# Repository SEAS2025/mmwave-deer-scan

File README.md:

# mmWave Deer Scan

Roadside **mmWave radar** deer detection for ambulance / fleet safety — companion to [agm-taipan-deer-scan](https://github.com/SEAS2025/agm-taipan-deer-scan) (thermal).

Detect deer from FMCW point clouds using size, speed, and SNR heuristics. Designed for **TI mmWave** UART JSON output and a **simulated** feed for development without hardware.

## Features

- Point-cloud clustering on sparse mmWave returns
- Deer-shaped target scoring (length, height, lateral position, speed)
- EGPWS-style threat callouts (left / ahead / right + range tier)
- TI mmWave serial reader (JSON lines) + OpenRadar raw-ADC adapter
- Thermal fusion (confirm with agm-taipan-deer-scan) and Pi GPIO/CAN alert outputs
- Session recorder for labeled training data
- Simulated roadside scene for offline development
- **Full hardware design**: system architecture, BOM, integration diagrams,
  dimensioned enclosure drawing, and a JLCPCB-ready carrier-board Gerber package
- **Imaging R&D track**: micro-Doppler + ISAR processing skeleton on raw ADC
  (`mmwave_deer/imaging/`), with a synthetic walking-deer demo

## Documentation & design

| Doc | What |
|-----|------|
| [docs/SYSTEM_DESIGN.md](docs/SYSTEM_DESIGN.md) | architecture, sensor/compute/power, requirements, risks |
| [docs/BOM.md](docs/BOM.md) / [docs/bom.csv](docs/bom.csv) | parts, links, cost roll-up (proto ~$400, prod target ~$140) |
| [docs/INTEGRATION.md](docs/INTEGRATION.md) | block diagram, power tree, GPIO map, wiring, sequence |
| [hardware/README.md](hardware/README.md) | enclosure drawing + carrier PCB |
| [hardware/enclosure/orthographic.svg](hardware/enclosure/orthographic.svg) | dimensioned 3-view drawing |
| [hardware/pcb/carrier_board/](hardware/pcb/carrier_board/) | Gerbers + `DeerWatch-Carrier-gerbers.zip` for JLCPCB |
| [hardware/pcb/carrier_board/kicad/](hardware/pcb/carrier_board/kicad/) | KiCad 10 project, DRC-clean, KiCad-exported Gerbers + 3D render |
| [docs/VARIANT_AWR1843.md](docs/VARIANT_AWR1843.md) | 77 GHz AWR1843BOOST variant - range math, config, carrier + BOM delta |
| [docs/IMAGING_RADAR_BOM.md](docs/IMAGING_RADAR_BOM.md) | imaging-radar tiers (raw capture / AWR2243 cascade / 4D) - parts + compute |

## Quick start

```powershell
cd mmwave-deer-scan
pip install -r requirements.txt
python scripts/live_scanner.py --demo
```

Or double-click `launch_scanner.bat`.

## Hardware

Primary target: **Texas Instruments mmWave EVM** (IWR6843 / AWR1843) with point-cloud UART JSON output.

1. Connect USB-UART (typically COM3 on Windows)
2. Edit `config/default.yaml` — set `reader.type: ti_mmwave` and `reader.port`
3. Run: `python scripts/live_scanner.py --reader ti_mmwave --port COM3`

On the Raspberry Pi with the carrier board (buzzer/LED + thermal fusion):

```bash
python scripts/live_scanner.py --reader ti_mmwave --port /dev/ttyACM0 --outputs --fusion confirm
```

## Record sessions

```powershell
python scripts/record_session.py --reader ti_mmwave --port COM3 --seconds 120
```

## Imaging (experimental)

Micro-Doppler signature + ISAR image formation from raw ADC. Runs on synthetic
data; feed a captured cube (DCA1000 / cascade) for real targets. See
[docs/IMAGING_RADAR_BOM.md](docs/IMAGING_RADAR_BOM.md).

```powershell
python scripts/microdoppler_demo.py --out samples
```

## Tests

```powershell
pytest tests/
```

## Related

- Thermal deer scan: https://github.com/SEAS2025/agm-taipan-deer-scan

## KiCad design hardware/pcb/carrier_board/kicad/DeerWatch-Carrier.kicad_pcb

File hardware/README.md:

# DeerWatch mmWave - Hardware

Hardware design for the roadside / vehicle deer early-warning unit. Full rationale in
[`../docs/SYSTEM_DESIGN.md`](../docs/SYSTEM_DESIGN.md).

## Contents

```
hardware/
  enclosure/
    gen_orthographic.py     # generates the dimensioned 3-view drawing
    orthographic.svg        # FRONT / TOP / RIGHT-SIDE with measurements (mm)
    orthographic_preview.png
    svg_to_png.py           # pure-Pillow SVG rasterizer (no cairo needed)
  pcb/
    carrier_board/
      gen_gerbers.py        # generates the full RS-274X + Excellon package
      gerbers/              # 60 GHz fab files       gerbers_awr1843/  # 77 GHz fab files
      DeerWatch-Carrier-gerbers.zip   # <- 60 GHz, upload to JLCPCB
      DeerWatch-CarrierHD-gerbers.zip # <- 77 GHz variant
      carrier_preview.png   carrier_preview_awr1843.png
      FAB_NOTES.md          # JLCPCB order settings + caveats
      gen_kicad.py          # emits the KiCad .kicad_pcb from the same layout
      kicad/                # KiCad 10 project: DRC-clean board + exported Gerbers + 3D render
        DeerWatch-Carrier.kicad_pcb   board_top.png   KICAD_NOTES.md
```

## Engineering drawing

Third-angle orthographic, all dims in mm. Enclosure envelope 160 x 90 x 60 mm,
RF radome window 80 x 50 mm, 5 deg boresight down-tilt.

```
python hardware/enclosure/gen_orthographic.py            # -> orthographic.svg
python hardware/enclosure/svg_to_png.py                  # -> orthographic_preview.png
```

Open `orthographic.svg` in any browser, Inkscape, or import to CAD.

## Carrier PCB

2-layer FR4, 70 x 50 mm. Power (12 V -> 5 V/5 A buck + 3V3 LDO), protection (fuse +
reverse-polarity FET + TVS), alert outputs (buzzer driver, RGB LED, MUTE), optional CAN,
and the Raspberry Pi 2x20 + radar headers.

```
python hardware/pcb/carrier_board/gen_gerbers.py                  # 60 GHz carrier
python hardware/pcb/carrier_board/gen_gerbers.py --variant awr1843 # 77 GHz carrier
```

Validated to parse cleanly with `gerbonara`. See
[`pcb/carrier_board/FAB_NOTES.md`](pcb/carrier_board/FAB_NOTES.md) for JLCPCB upload.

### KiCad project (full routing + DRC)

The board is also generated as a real KiCad 10 project and design-rule-checked
with KiCad's own engine (**0 violations**; GND poured, power core routed, signal
ratsnest left for interactive routing). See
[`pcb/carrier_board/kicad/KICAD_NOTES.md`](pcb/carrier_board/kicad/KICAD_NOTES.md).

```
python hardware/pcb/carrier_board/gen_kicad.py
kicad-cli pcb drc DeerWatch-Carrier.kicad_pcb
kicad-cli pcb export gerbers -o kicad_gerbers --no-protel-ext DeerWatch-Carrier.kicad_pcb
```

> The 60/77 GHz RF front end is a certified COTS module (TI IWR6843AOPEVM), not a custom
> RF board. The carrier handles everything below RF.

## Bill of materials

See [`../docs/BOM.md`](../docs/BOM.md) (+ [`../docs/bom.csv`](../docs/bom.csv)) for the full
parts list, links, and cost roll-up (prototype ~$400, production target ~$140).

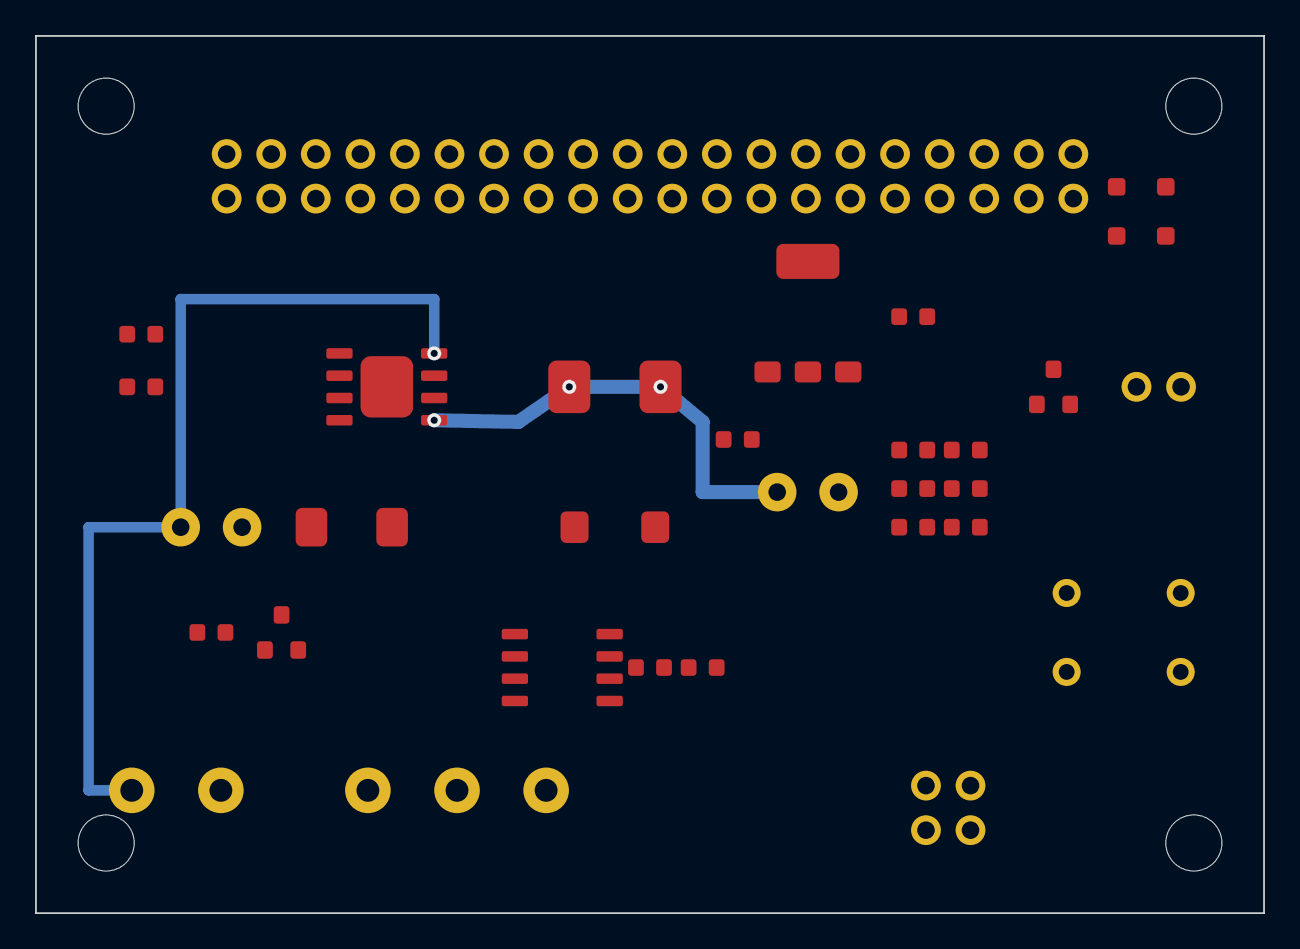
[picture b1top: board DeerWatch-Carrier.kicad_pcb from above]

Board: 2 copper layers, 70.0 x 50.0 mm, 34 parts (0 on the bottom side), 6 nets.

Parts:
BZ1: BUZZER; BZ1
C1: 100uF; C1
C2: 100uF; C2
C3: 100nF; C3
C4: 100nF; C4
C5: 100nF; C5
C6: 100nF; C6
C7: 100nF; C7
C8: 100nF; C8
C9: 100nF; C9
D1: SMBJ16A; D1
D2: SS34; D2
D3: RGB5050; D3
J1: 12V_IN; J1
J2: CAN; J2
J3: RPi_2x20; J3
J4: RADAR; J4
L1: 10uH; L1
MH1: M3; MH1
MH2: M3; MH2
MH3: M3; MH3
MH4: M3; MH4
Q1: P-FET; Q1
Q2: NPN; Q2
R1: 0603; R1
R2: 0603; R2
R3: 0603; R3
R4: 0603; R4
R5: 0603; R5
R6: 0603; R6
SW1: TACT; SW1
U1: TPS5450; U1
U2: AMS1117-3.3; U2
U3: SN65HVD230; U3

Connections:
+3V3: J3.1, J3.17, U2.2, U2.4, U3.3
+5V: C2.1, D2.2, D3.1, J3.2, J3.4, J4.1, L1.1, L1.2, U1.5, U2.3
+12V: C1.1, D1.1, J1.1, Q1.2, Q1.3, U1.8
CANH: J2.1, U3.7
CANL: J2.2, U3.6
GND: BZ1.2, C1.2, C2.2, D1.2, D2.1, J1.2, J2.3, J3.6, J3.9, J3.14, J3.20, J3.25, J3.30, J3.34, J3.39, J4.2, Q2.2, SW1.1, SW1.3, U1.3, U1.9, U2.1, U3.2
